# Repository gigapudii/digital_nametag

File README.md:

# Digital nametag
A digital nametag based on the Nokia 3310 screen, making you interesting during fairs.

## WHY
Whenever I visit fairs, I often feel that I am not noticed very much. And when I do find someone to speak to, I sometimes find it hard to start a conversation. 

## HOW
The solution is a digital nametag. It can be used as a conversation starter and help show your creativity to the public. Aside of this, it gives you the possibility to present parts of your CV as well as contact information without having to spell it out loud everytime.

For the nametag you will need a screen to begin with. Nokia 3310 screens are big enough and apparently still sold online. Aside of this, you will need an Attiny85, a coin cell battery (CR2032), an on/off switch, and a button to power up the backlight of the screen. 

As for the microcontroller, the Attiny85 is preferred because it's a) low powered b) cheap and c) has just enough pins to drive the screen.

To design the board, Eagle CAD was used. The basic thought during the design process was to make it "invisible", i.e. have it hidden behind the screen, and for it to have a small cut on the top to be hanged through. Apart from this, the most important part was to make the correct connections between the board and the screen which was fairly straight forward. 

As for the software, the screen is controlled through an [Arduino library](https://github.com/platisd/nokia-5110-lcd-library). Additionally, when the screen is not updated, the microcontroller is in deep sleep to preserve the battery.

To create the images that were displayed on the screen, Adobe Photoshop and the LCD Assistant were mainly used.

## Components
* [Nametag PCB](https://oshpark.com/shared_projects/H9KOpiVm)
* Attiny85
* Coin cell battery CR2032
* Coin cell battery holder
* On/off switch
* Backlight button
* Resistor (for the backlight)

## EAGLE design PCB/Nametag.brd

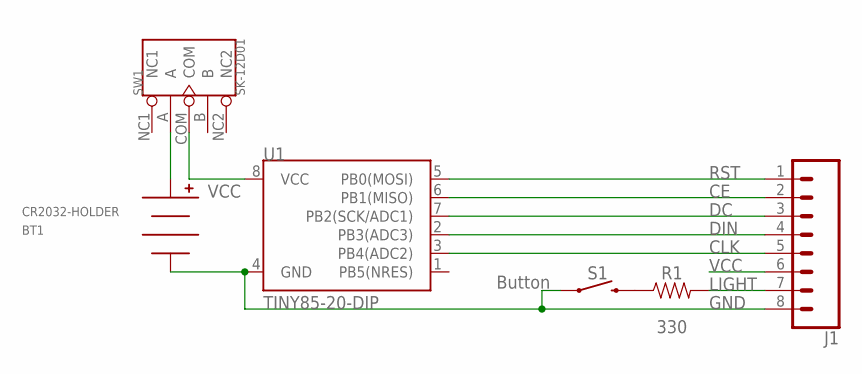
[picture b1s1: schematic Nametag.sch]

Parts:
BT1: CR2032-HOLDER; CH28-2032LF
J1: CONN_08"; 1X08
R1: 330; AXIAL-0.3
S1: Button; TACTILE_SWITCH_PTH_6.0MM
SW1: SK-12D01; SW5-2.0-8.8X4.4X4.7MM-90D
U1: TINY85-20-DIP; DIP08_MCU

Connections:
CE: J1.2, U1.6 (PB1(MISO))
CLK: J1.5, U1.3 (PB4(ADC2))
DC: J1.3, U1.7 (PB2(SCK/ADC1))
DIN: J1.4, U1.2 (PB3(ADC3))
GND: BT1.NEG, J1.8, S1.1, U1.4 (GND)
LIGHT: J1.7, R1.P$2 (2)
unnamed: R1.P$1 (1), S1.3 (2)
unnamed: BT1.POS, SW1.A
RST: J1.1, U1.5 (PB0(MOSI))
VCC: J1.6, SW1.COM, U1.8 (VCC)

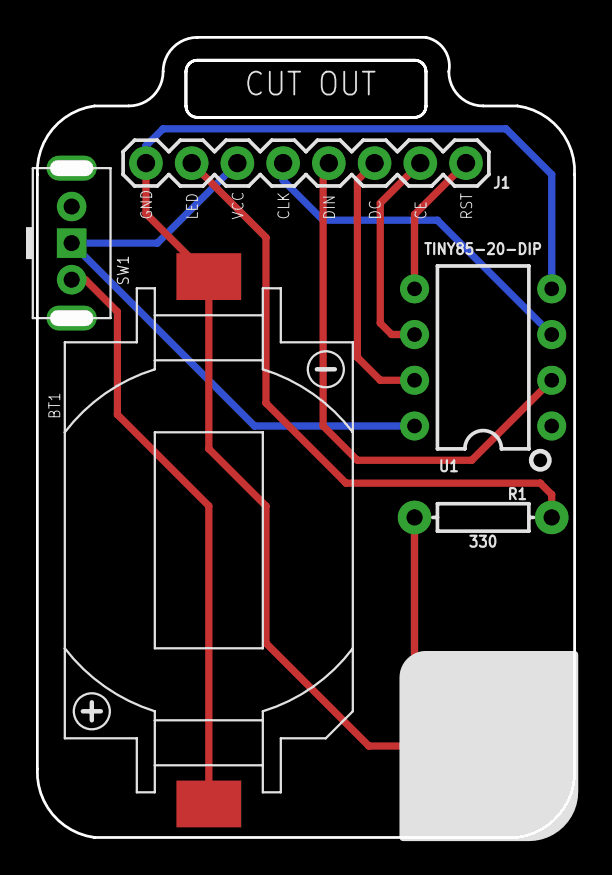
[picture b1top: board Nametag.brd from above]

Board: 2 copper layers, 29.8 x 44.5 mm, 6 parts (0 on the bottom side), 10 nets.

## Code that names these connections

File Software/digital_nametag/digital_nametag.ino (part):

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};

Nokia_LCD lcd(PB4 /* CLK */, PB3 /* DIN */, PB2 /* DC */, PB1 /* CE */, PB0 /* RST */);

volatile bool watchdogBarked = false;

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
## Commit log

2018-09-02 add first version of README.md
2018-09-02 add arduino sketch
2018-09-02 add PCB
2018-09-02 add link to osh park
2018-09-02 add license
2018-09-03 add photos
2018-09-03 add new links to photos
2018-09-03 updated one photo link
2018-09-03 move sketch folder one step up
2018-09-06 Update text

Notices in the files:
parts and their libraries:
SparkFun-Connectors: Licensing: Creative Commons ShareAlike 4.0 International - https://creativecommons.org/licenses/by-sa/4.0
